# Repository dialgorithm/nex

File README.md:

# nex

**nex** is a swarm robotics project built around **ESP32-based bots**, computer vision, AprilTags, and a custom 4-layer PCB. The goal is to have multiple small bots identify and communicate with each other while working together as a swarm.

it features:

- ESP32-WROOM in each bot for wireless communication
- Luckfox Lyra Zero W for computer vision
- AprilTags for identifying individual bots
- Custom 4-layer PCB designed in KiCad

## how it works

each bot has an **ESP32-WROOM** which handles communication between the bots and provides the wireless connection. Each bot also has its own AprilTag, giving the vision system a way to identify which bot it is looking at.

the **Luckfox Lyra Zero W** handles the computer vision side. It detects the AprilTags and uses their position and orientation to work out where the other bots are.

this allows the bots to know who is around them and where they are, which forms the basis for the swarm behaviour.

## KiCad

the electronics are built around a custom **4-layer PCB**, designed to keep the different parts of the bot connected without needing a large amount of external wiring.

|              schematic              |           PCB           |
| :---------------------------------: | :---------------------: |
|  |  |

|        PCB mockup top         |          PCB mockup bottom          |
| :---------------------------: | :---------------------------------: |
|  |  |

## Fusion

the mechanical design and overall bot layout were modelled in Fusion.

|             top              |              side              |               bottom               |
| :--------------------------: | :----------------------------: | :--------------------------------: |
|  |  |  |

## BOM

the complete bill of materials is available in [`bom.csv`](bom.csv).

## firmware

firmware is not included yet. The software will be added after the physical bots are built and the hardware can be tested and debugged.

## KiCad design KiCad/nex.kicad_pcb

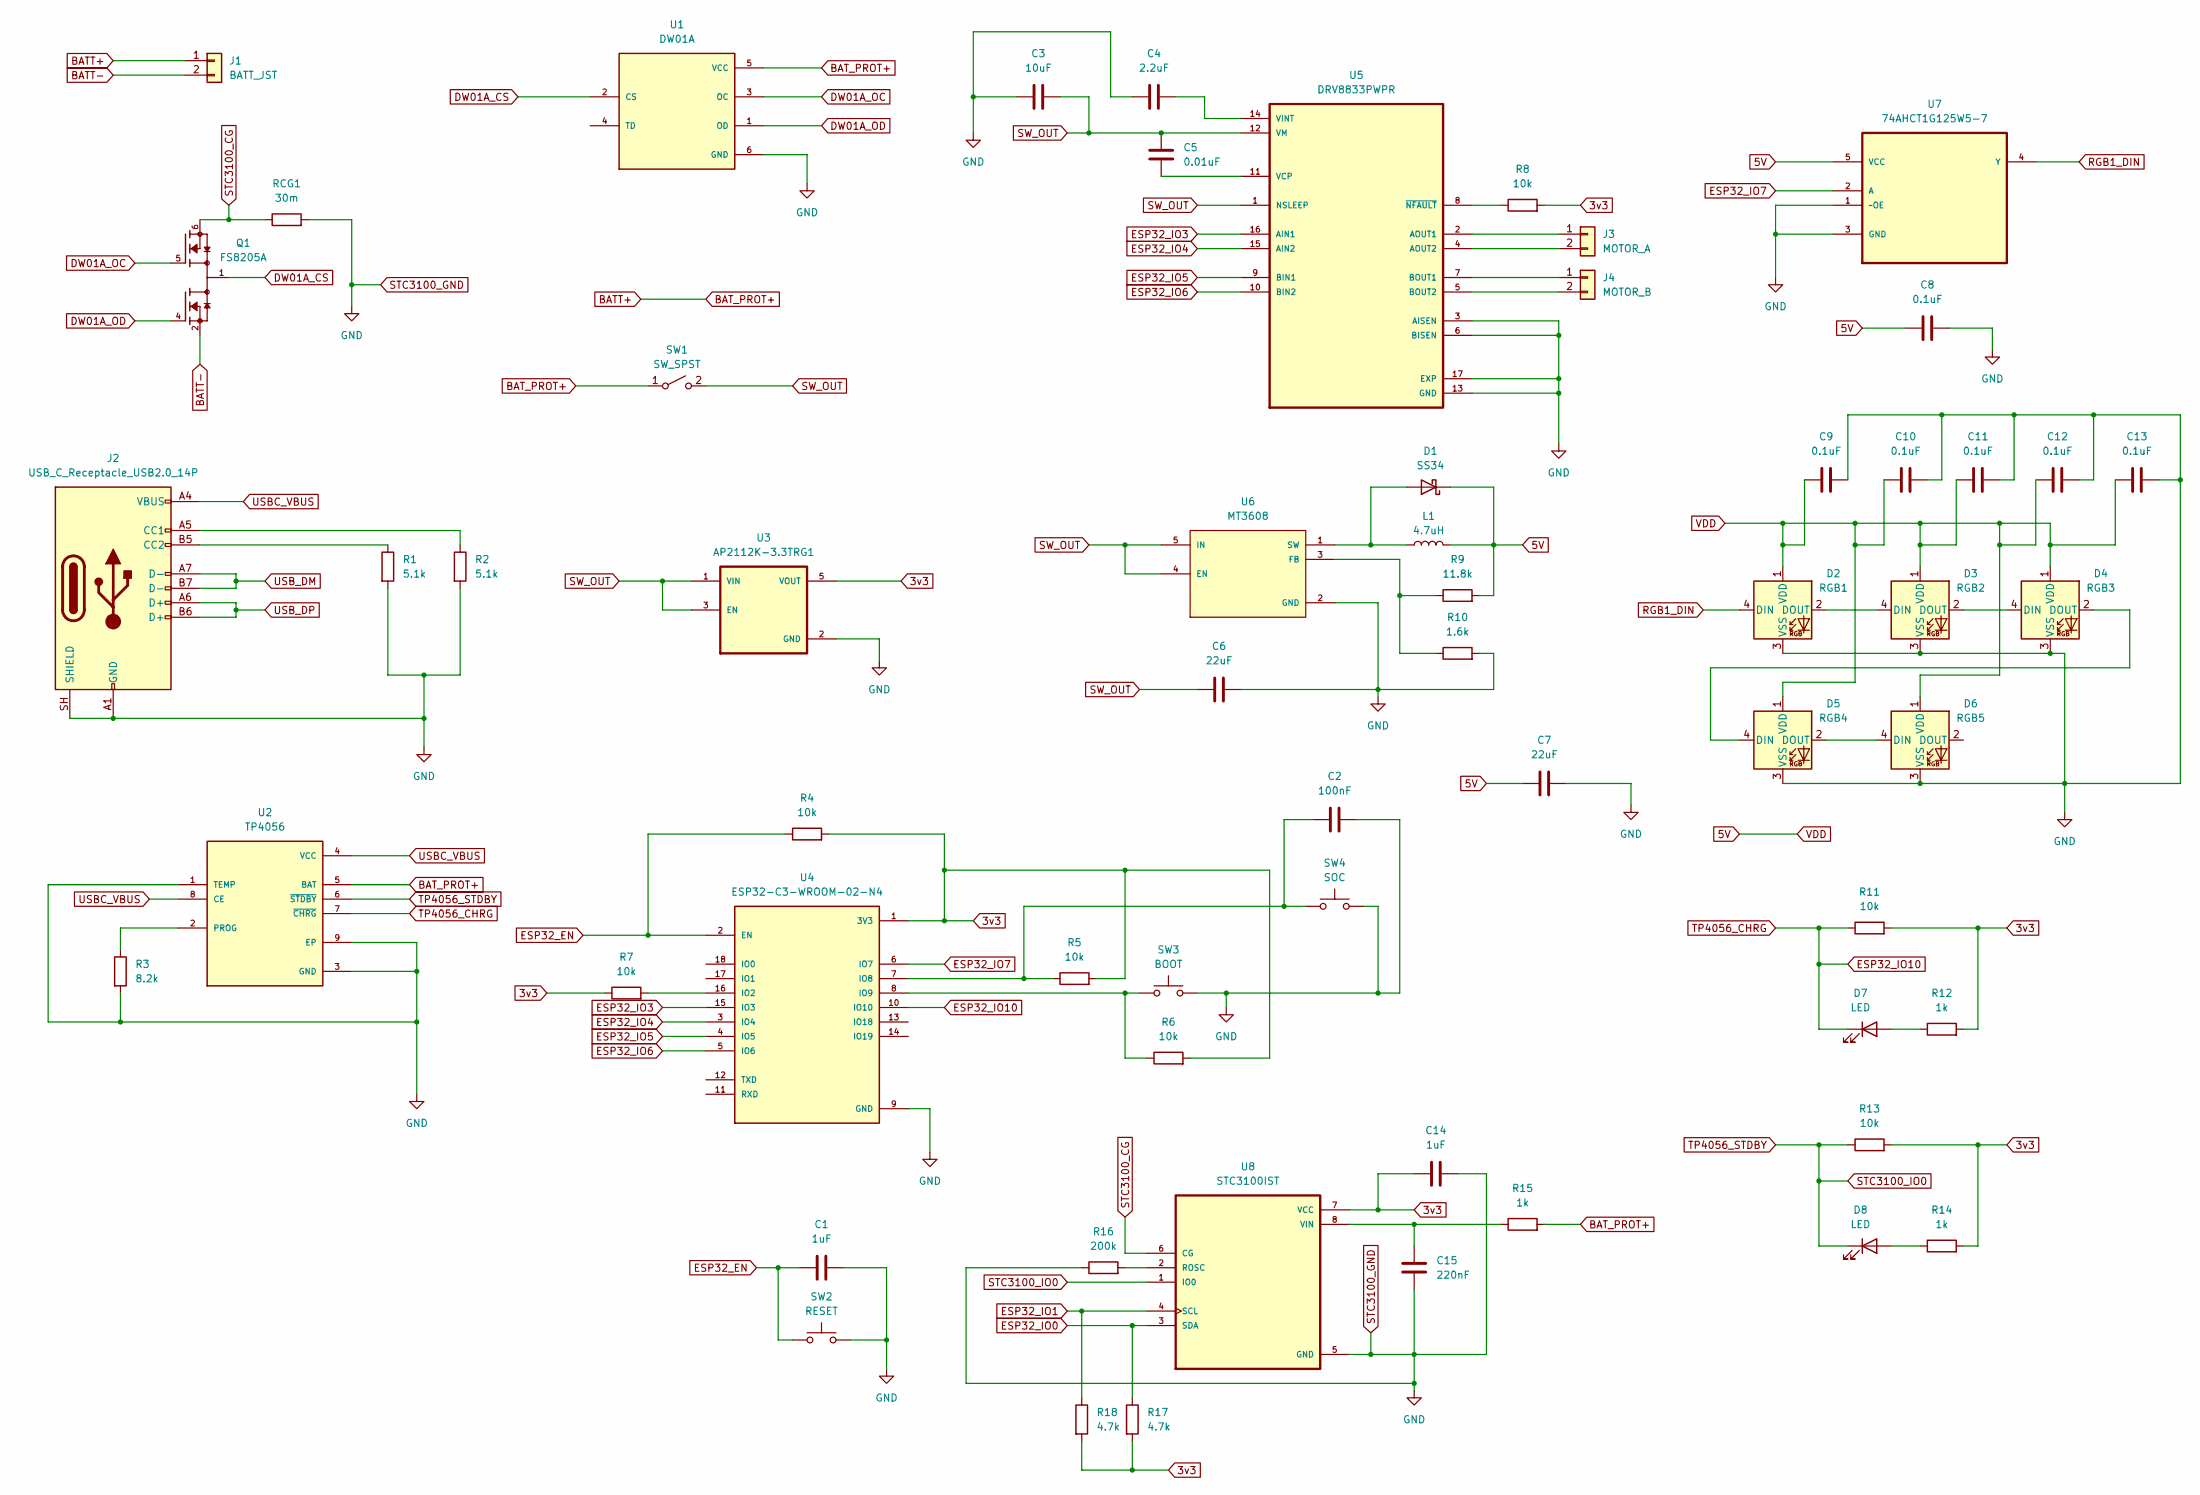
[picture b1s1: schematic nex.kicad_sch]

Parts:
C1, C14: 1uF; C_1206_3216Metric
C2: 100nF; C_1206_3216Metric
C3: 10uF; C_1206_3216Metric
C4: 2.2uF; C_1206_3216Metric
C5: 0.01uF; C_1206_3216Metric
C6, C7: 22uF; C_1206_3216Metric
C8, C9, C10, C11, C12, C13: 0.1uF; C_1206_3216Metric
C15: 220nF; C_1206_3216Metric
D1: SS34; D_SMA
D2: RGB1; LED_WS2812B_PLCC4_5.0x5.0mm_P3.2mm
D3: RGB2; LED_WS2812B_PLCC4_5.0x5.0mm_P3.2mm
D4: RGB3; LED_WS2812B_PLCC4_5.0x5.0mm_P3.2mm
D5: RGB4; LED_WS2812B_PLCC4_5.0x5.0mm_P3.2mm
D6: RGB5; LED_WS2812B_PLCC4_5.0x5.0mm_P3.2mm
D7, D8: LED; LED_1206_3216Metric
J1: BATT_JST; JST_PH_S2B-PH-K_1x02_P2.00mm_Horizontal
J2: USB_C_Receptacle_USB2.0_14P; USB_C_Receptacle_GCT_USB4105-xx-A_16P_TopMnt_Horizontal
J3: MOTOR_A; JST_PH_S2B-PH-K_1x02_P2.00mm_Horizontal
J4: MOTOR_B; JST_PH_S2B-PH-K_1x02_P2.00mm_Horizontal
L1: 4.7uH; L_1210_3225Metric
Q1: FS8205A; SOP65P640X120-8N; PARTREV 1.7
R1, R2: 5.1k; R_1206_3216Metric
R3: 8.2k; R_1206_3216Metric
R4, R5, R6, R7, R8, R11, R13: 10k; R_1206_3216Metric
R9: 11.8k; R_1206_3216Metric
R10: 1.6k; R_1206_3216Metric
R12, R14, R15: 1k; R_1206_3216Metric
R16: 200k; R_1206_3216Metric
R17, R18: 4.7k; R_1206_3216Metric
RCG1: 30m; R_1206_3216Metric
SW1: SW_SPST; SW_DIP_SPSTx01_Slide_6.7x4.1mm_W6.73mm_P2.54mm_LowProfile_J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
SW2: RESET; SW_SPST_B3U-1000P
SW3: BOOT; SW_SPST_B3U-1000P
SW4: SOC; SW_SPST_B3U-1000P
U1: DW01A; SOT95P280X145-6N; PARTREV 1.8
U2: TP4056; SOP127P600X175-9N
U3: AP2112K-3.3TRG1; SOT95P285X140-5N; PARTREV 2-2
U4: ESP32-C3-WROOM-02-N4; MODULE_ESP32-C3-WROOM-02-H4
U5: DRV8833PWPR; IC_DRV8833PWPR; PARTREV E
U6: MT3608; SOT95P280X145-6N; PARTREV 1.0
U7: 74AHCT1G125W5-7; SOT95P280X140-5N; MPN 74AHCT1G125W5-7
U8: STC3100IST; SOIC65P490X110-8N

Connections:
3v3: C14.1, R4.2, R5.2, R6.2, R7.1, R8.2, R11.2, R12.2, R13.2, R14.2, R17.2, R18.2, U3.5 (VOUT), U4.1 (3V3), U8.7 (VCC)
5V: C7.1, C8.1, C9.1, C10.1, C11.1, C12.1, C13.1, D1.1 (K), D2.1 (VDD), D3.1 (VDD), D4.1 (VDD), D5.1 (VDD), D6.1 (VDD), L1.2, R9.2, U7.5 (VCC)
BATT+: J1.1, R15.2, SW1.1 (A), U1.5 (VCC), U2.5 (BAT)
BATT-: J1.2, Q1.2, Q1.3
DW01A_CS: Q1.1, Q1.8, U1.2 (CS)
DW01A_OC: Q1.5, U1.3 (OC)
DW01A_OD: Q1.4, U1.1 (OD)
ESP32_EN: C1.1, R4.1, SW2.1, U4.2 (EN)
ESP32_IO0: R17.1, U8.3 (SDA)
ESP32_IO1: R18.1, U8.4 (SCL)
ESP32_IO3: U4.15 (IO3), U5.16 (AIN1)
ESP32_IO4: U4.3 (IO4), U5.15 (AIN2)
ESP32_IO5: U4.4 (IO5), U5.9 (BIN1)
ESP32_IO6: U4.5 (IO6), U5.10 (BIN2)
ESP32_IO7: U4.6 (IO7), U7.2 (A)
ESP32_IO10: D7.1 (K), R11.1, U2.7 (~CHRG), U4.10 (IO10)
unnamed: D1.2 (A), L1.1, U6.1 (SW)
unnamed: D2.2 (DOUT), D3.4 (DIN)
unnamed: D3.2 (DOUT), D4.4 (DIN)
unnamed: D4.2 (DOUT), D5.4 (DIN)
unnamed: D5.2 (DOUT), D6.4 (DIN)
unnamed: D7.2 (A), R12.1
unnamed: D8.2 (A), R14.1
unnamed: J2.A5 (CC1), R2.1
unnamed: J2.B5 (CC2), R1.1
unnamed: J3.1, U5.2 (AOUT1)
unnamed: J3.2, U5.4 (AOUT2)
unnamed: J4.1, U5.7 (BOUT1)
unnamed: J4.2, U5.5 (BOUT2)
unnamed: R3.1, U2.2 (PROG)
unnamed: R7.2, U4.16 (IO2)
unnamed: C2.1, R5.1, SW4.1, U4.7 (IO8)
unnamed: R6.1, SW3.1, U4.8 (IO9)
unnamed: C5.1, U5.11 (VCP)
unnamed: C4.2, U5.14 (VINT)
unnamed: R8.1, U5.8 (~NFAULT)
unnamed: R9.1, R10.1, U6.3 (FB)
unnamed: R16.2, U8.2 (ROSC)
unnamed: C15.2, R15.1, U8.8 (VIN)
RGB1_DIN: D2.4 (DIN), U7.4 (Y)
STC3100_CG: Q1.6, Q1.7, RCG1.1, U8.6 (CG)
STC3100_GND: C1.2, C2.2, C3.1, C4.1, C6.2, C7.2, C8.2, C9.2, C10.2, C11.2, C12.2, C13.2, C14.2, C15.1, D2.3 (VSS), D3.3 (VSS), D4.3 (VSS), D5.3 (VSS), D6.3 (VSS), J2.A1 (GND), J2.A12 (GND), J2.B1 (GND), J2.B12 (GND), J2.SH (SHIELD), R1.2, R2.2, R3.2, R10.2, R16.1, RCG1.2, SW2.2, SW3.2, SW4.2, U1.6 (GND), U2.1 (TEMP), U2.3 (GND), U2.9 (EP), U3.2 (GND), U4.9 (GND), U4.19 (GND), U4.20 (GND), U4.21 (GND), U4.22 (GND), U4.23 (GND), U4.24 (GND), U4.25 (GND), U4.26 (GND), U4.27 (GND), U4.28 (GND), U4.29 (GND), U4.30 (GND), U4.31 (GND), U4.32 (GND), U4.33 (GND), U4.34 (GND), U4.35 (GND), U4.36 (GND), U4.37 (GND), U4.38 (GND), U4.39 (GND), U5.3 (AISEN), U5.6 (BISEN), U5.13 (GND), U5.17 (EXP), U6.2 (GND), U7.1 (~OE), U7.3 (GND), U8.5 (GND)
STC3100_IO0: D8.1 (K), R13.1, U2.6 (~STDBY), U8.1 (IO0)
SW_OUT: C3.2, C5.2, C6.1, SW1.2 (B), U3.1 (VIN), U3.3 (EN), U5.1 (NSLEEP), U5.12 (VM), U6.4 (EN), U6.5 (IN)
USBC_VBUS: J2.A4 (VBUS), J2.A9 (VBUS), J2.B4 (VBUS), J2.B9 (VBUS), U2.4 (VCC), U2.8 (CE)
USB_DM: J2.A7 (D-), J2.B7 (D-)
USB_DP: J2.A6 (D+), J2.B6 (D+)

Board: 2 copper layers, 60 parts (27 on the bottom side), 47 nets, no tracks yet.
